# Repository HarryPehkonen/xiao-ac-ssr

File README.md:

# xiao-ac-ssr

One-channel inline AC **solid-state switch** (on/off, no dimming) for a Seeed
Studio XIAO ESP32C3 (or any XIAO on the same 14-pad footprint). Mains cord in
one end, load socket out the other, and a zero-cross opto-triac driving a
snubberless triac switches whatever is plugged in between them. Plug-in
bench/room scale — not house wiring.

Same family as [`xiao-ac-dimmer`](https://github.com/HarryPehkonen/xiao-ac-dimmer):
the whole mains front end, the XIAO sockets, the generator/router pipeline and
the gates are copied; the switching element and everything that existed only to
support *dimming* are replaced.

**Status: schematic and board complete and machine-checked. The board is
150 × 45 mm (67.5 cm²), 11/11 nets routed, DRC clean — 0 errors, 0 warnings.
Gerbers exported but not yet eyeballed in a gerber viewer and not yet checked by
a fab's DFM rules.**

## Why an SSR and not a relay

Mechanical relay contact life at rated load is ~10⁵ operations; 100
activations a day reaches that in a few years, and the contacts weld rather
than fail safe-ly. A triac has no moving contacts. (Seeed's own XIAO relay
module quotes 1.5 × 10⁴ operations at 10 A/250 VAC *resistive* — electrical
endurance, not the headline mechanical number.)

The one thing a triac does **worse** than a relay is fail: it fails **short**,
so the load stays on and software cannot turn it off. See *Safety* below.

## No dimming, therefore much less circuit

Relative to the dimmer, this board **deletes** the H11AA1 zero-cross detector,
both 47 k detector legs, the 10 k pull-up, the 100 Ω + 100 nF triac snubber and
the phase-control firmware — six parts and five nets, all of them on the mains
side. What replaces them:

| | dimmer | this board |
| --- | --- | --- |
| opto | MOC3021M, *random phase* | **MOC3063M, *zero cross*** |
| triac | BTA16-600B, I_GT 50 mA | **BTA16-600SW, I_GT 10 mA, snubberless** |
| gate resistor | 1 k | **360 Ω** (onsemi's own figure-10 value) |
| LED resistor | 220 Ω | **150 Ω** |
| snubber | 100 Ω + 100 nF | none — not needed, see DESIGN.md |
| zero-cross input | H11AA1 on D2 | none; D2 is unused |

The two parts that changed are not cosmetic. A zero-cross opto only conducts
inside a ±12 V (typ) / ±20 V (max) window around the crossing, so the current it
can push into the triac's gate is bounded by that window divided by the gate
resistor. See DESIGN.md for the arithmetic — it is why the *standard* triac
(BTA16-600B, I_GT up to 50 mA) is the wrong part in this position.

## The schematic is generated

`xiao-ac-ssr.kicad_sch` is written by `tools/gen_sch.py`. The circuit lives
there as a table of parts and nets; the generator draws each symbol, a stub wire
per pin and a label naming that pin's net. Open the result in KiCad 9 to review
it like any other schematic.

That indirection is deliberate: a hand-drawn schematic cannot be verified, and
a generated one can (see Gates).

## Gates

```sh
./tools/ci.sh
```

1. **Generator == committed file.** Regenerating leaves `xiao-ac-ssr.kicad_sch`
   and `symbols/xiao-ac.kicad_sym` byte-identical, so neither the committed
   schematic nor the symbol library it draws `J1`/`J2` from is ever stale.
2. **Netlist == intent.** `tools/check_netlist.py` exports a netlist with
   `kicad-cli` and asserts it against the intended netlist: every net present
   with exactly the intended pins, no unintended net at all (that would be a
   short), only the deliberately open pins reported unconnected, and every pin
   of the two XIAO socket rows carrying the *module's* pin name — `D0..D6` on
   `J1`, `VBUS, GND, 3V3_OUT, D10, D9/BOOT, D8, D7` on `J2` — so the schematic
   and its netlist say which pin is which instead of leaving it to a comment.
3. **ERC clean.** `kicad-cli sch erc` reports 0 violations.
4. **Board DRC clean.** `tools/check_board.py` — 0 errors, 0 warnings, including
   the 3 mm mains/logic clearance rule in `xiao-ac-ssr.kicad_dru`.
5. **Board == generator.** `tools/check_regen.py` regenerates the board in a
   throwaway copy of the tools and compares every footprint and every copper
   item against the committed board — 18 footprints (14 parts + 4 mounting
   holes) and 143 tracks+vias today.
   The board file is not *byte*-reproducible (pcbnew stamps fresh UUIDs and
   writes items in its own order), so this compares geometry, which is the part
   a person would have had to edit. `docs/PCB-NOTES.md` has the measurement.
6. **The gates' own tests.** `tools/tests/test_board_gate.py` breaks each
   rule that check 4 enforces — a moved or renamed hole, a track or pad inside
   the keepout, a hole tied to a net, a plated or undersized hole, a footprint
   id with no library nickname, a missing hole — and asserts `check_board.py`
   reports it. `tools/tests/test_pin_names.py` does the same for check 2's pin
   names: a renamed pin, the rows back to `Pin_1..Pin_7`, a renumbered row.
   A rule that has never been seen to fail is not a gate.

Fabrication data:

```sh
./tools/gerbers.sh          # build/gerbers/ + build/xiao-ac-ssr-gerbers.zip
```

## Circuit in one paragraph

Cord hot goes through a 3.15 A fuse, then feeds an MOV, the HLK-PM01's AC input
and the triac's A1; neutral runs straight through to the outlet, unswitched. The
HLK's isolated 5 V reaches the XIAO's VBUS pad through a Schottky diode. GPIO3
(D1) drives the MOC3063M's LED through 150 Ω; the opto's output waits for the
line to cross zero, then pushes current through 360 Ω into the BTA16-600SW's
gate, and the triac conducts the rest of the half-cycle. Part-by-part reasoning,
including the gate-drive arithmetic and what is deliberately *not* proven:
DESIGN.md.

## Bill of materials (all through-hole, 16 parts)

| Ref | Part | Note |
| --- | --- | --- |
| PS1 | HLK-PM01 | isolated 100–240 VAC → 5 V 0.6 A |
| F1 | 5×20 mm fuse clip + 3.15 A slow-blow | hot leg only |
| MOV1 | S14K150 varistor | 150 VAC rating |
| Q1 | BTA16-600SW | TO-220, snubberless logic level, I_GT 10 mA |
| U2 | MOC3063M | *zero-cross* opto-triac, DIP-6 |
| D5 | SS14 | Schottky, VBUS feed |
| R3 | 150 Ω | opto LED from 3.3 V (≈12 mA vs 5 mA I_FT) |
| R4 | 360 Ω | triac gate |
| C1 | 470 µF 16 V | 5 V bulk |
| C2 | 100 nF | XIAO decoupling |
| J1, J2 | 2 × 1×07 2.54 mm socket | XIAO: J1 = D0..D6, J2 = 5V..D7 |
| J3, J4 | 2-pole 5.08 mm screw terminal | cord in / load out |

Where to buy each one, and why: BOM.md.

## Safety — read before powering anything up

- The hot is switched and fused; the neutral is never broken and never fused
  on its own. Mains and logic copper are separated by a 3 mm rule *and* a routed
  isolation slot; nothing on the logic side is ever referenced to mains.
- **A triac fails short.** If Q1 or U2 dies, the load stays energised and no
  software can turn it off. Put a mechanical switch (or a switched cord) between
  the wall and this box, or accept that the only off switch is the breaker.
  A relay fails open instead; this is the price of a moving-contact-free switch.
- **Never work on it live. First power-up on a GFCI/RCD outlet. Never flash
  firmware with mains connected.** Insulation test (500 V) before first
  power-up if a megger is available.
- 3.15 A suits a ~60 W lamp; the ceiling is ~378 W at 120 V because that is what
  1.5 mm mains copper carries at a 10 °C rise (IPC-2221). Larger loads need the
  fuse, the copper *and* the triac's heatsinking rechecked — and the copper is
  currently the binding limit (see DESIGN.md, "the current ceiling").
- Size for **inrush**, not steady wattage: LED drivers and motors pull 10–20×.
  The triac is a 16 A part and will take it; the fuse is slow-blow for the same
  reason.
- Nothing here is a safety certification. The insulation barrier is the
  HLK-PM01, the opto and the layout, and the enclosure is yours. Plastic
  standoffs and a plastic box, never earthed metal.

## Files

```
xiao-ac-ssr.kicad_sch      generated schematic (the reviewable design)
xiao-ac-ssr.kicad_pcb      generated board -- never hand-edit
xiao-ac-ssr.kicad_dru      the 3 mm mains/logic barrier and the 1.5 mm mains width
xiao-ac-ssr.kicad_pro      project + netclass settings
symbols/xiao-ac.kicad_sym  the socket rows' symbols, pins named D0..D6 / VBUS..D7
sym-lib-table fp-lib-table so the libraries resolve without global config
tools/kicadlib.py          s-expression reader, symbol flattening (extends)
tools/gen_sch.py           the circuit + schematic generator
tools/gen_pcb.py           placement + board generator
tools/route.py             the maze router
tools/check_netlist.py     gate: exported netlist == intended netlist (and pin names)
tools/check_board.py       gate: kicad-cli pcb drc, exit 0 = no violations
tools/check_regen.py       gate: committed board == generated board (geometry)
tools/ci.sh                the gates
tools/gerbers.sh           fab output (gerbers, drill, zip)
tools/preview.sh           schematic svg/pdf + board svg, for human eyes
tools/zipdir.py            zip the gerber bundle (zip(1) is not installed here)
docs/PCB-NOTES.md          board status, and what the router needed
docs/ninny-brief.md        the next slice, briefed for a test-first agent
DESIGN.md                  engineering decisions and open items
BOM.md                     sourcing and mechanical notes
```

## Requirements

KiCad 9 (`kicad-cli`) and its Python bindings for the board step; ngspice is not
needed for this board:

```sh
sudo apt-get install kicad kicad-symbols kicad-footprints
```

Regenerate: `python3 tools/gen_sch.py`, then `/usr/bin/python3 tools/gen_pcb.py`
(the `pcbnew` bindings are not in a venv here).

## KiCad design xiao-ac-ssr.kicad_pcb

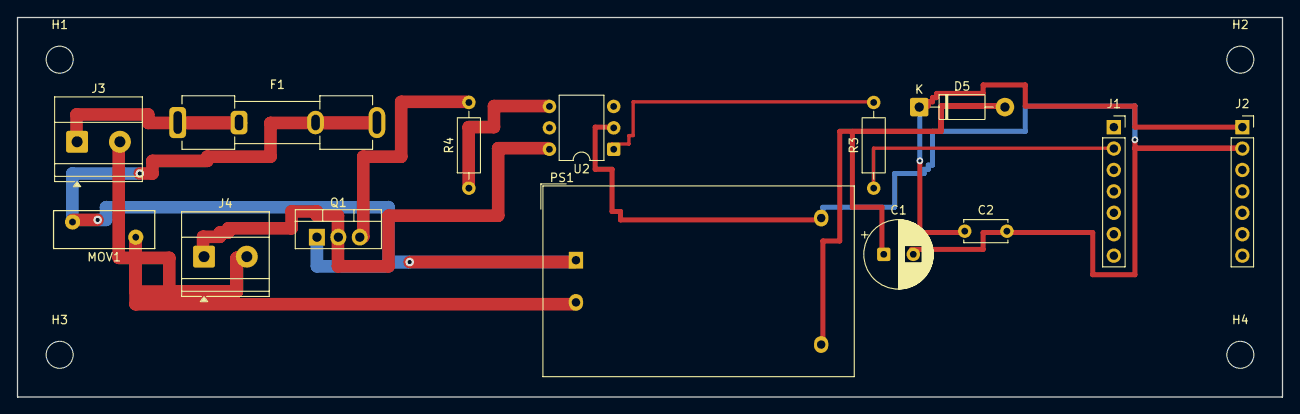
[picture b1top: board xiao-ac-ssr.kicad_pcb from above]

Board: 2 copper layers, 150.0 x 45.0 mm, 18 parts (0 on the bottom side), 11 nets.

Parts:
C1: 470uF 16V; CP_Radial_D8.0mm_P3.50mm
C2: 100nF; C_Disc_D5.0mm_W2.5mm_P5.00mm
D5: SS14; D_DO-41_SOD81_P10.16mm_Horizontal
F1: 3.15A; Fuseholder_Clip-5x20mm_Keystone_3512P_Inline_P23.62x7.27mm_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
H1, H2, H3, H4: MountingHole_3.2mm_M3
J1: XIAO-ESP32C3 left D0..D6; PinSocket_1x07_P2.54mm_Vertical
J2: XIAO-ESP32C3 right 5V..D7; PinSocket_1x07_P2.54mm_Vertical
J3: AC IN (cord); TerminalBlock_Phoenix_MKDS-1,5-2-5.08_1x02_P5.08mm_Horizont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
J4: AC OUT (load); TerminalBlock_Phoenix_MKDS-1,5-2-5.08_1x02_P5.08mm_Horizont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
MOV1: S14K150; RV_Disc_D12mm_W4.5mm_P7.5mm
PS1: HLK-PM01 5V 0.6A; Converter_ACDC_Hi-Link_HLK-PMxx
Q1: BTA16-600SW; TO-220-3_Vertical
R3: 150; R_Axial_DIN0207_L6.3mm_D2.5mm_P10.16mm_Horizontal
R4: 360; R_Axial_DIN0207_L6.3mm_D2.5mm_P10.16mm_Horizontal
U2: MOC3063M; DIP-6_W7.62mm

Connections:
+5V_PS: C1.1, D5.2, PS1.4
+5V_XIAO: C2.1, D5.1, J2.1
GATE_DRV: J1.2, R3.1
GND: C1.2, C2.2, J2.2, PS1.3, U2.2
LOAD_L: J4.1, Q1.2, U2.6
L_FUSED: F1.2, MOV1.1, PS1.1, Q1.1
L_IN: F1.1, J3.1
MOC_A: R3.2, U2.1
MOC_MT2: R4.1, U2.4
N_AC: J3.2, J4.2, MOV1.2, PS1.2
TRIAC_G: Q1.3, R4.2

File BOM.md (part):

# BOM — one board

Generated from the schematic, not typed from memory:

```bash
kicad-cli sch export bom --fields "Reference,Value,Footprint" \
  -o bom.csv xiao-ac-ssr.kicad_sch
```

16 parts. `bom.csv` is the source of truth for values and footprints; this file
adds the part of the BOM a generator cannot know: **where to buy it, and what it
costs to get it here.**

## The sourcing rule

> **Consolidate to the fewest orders first. Origin is a tiebreaker on price, not
> an absolute.** A US-origin part that saves a shipment wins; a $6 saving that
> creates a second shipment loses.

Two constraints in tension, both Harri's:

1. **Non-US origin preferred** — US-origin parts carry tariff and political
   cost. DigiKey's Canadian presence is welcome as a *channel* (one shipment,
   CAD pricing, traceability), not as a statement about origin.
2. **Shipping is per-supplier and it is not small.** DigiKey CA: **free delivery
   at $100 CAD or more; about $15 CAD below that** (their delivery page states
   the $100 threshold; the sub-$100 charge has been reported rising to $15).

So a BOM can carry more shipping than parts. Two ways out: **pad the order over
$100** (spares of the passives are nearly free, and more boards are coming), or
**accept the charge once** rather than paying it several times.

## Where each part comes from

| Source | Parts |
| --- | --- |
| **DigiKey CA** (one order) | `C1` 470 µF 16 V · `C2` 100 nF · `D5` SS14 · `F1` 5×20 mm fuseholder clip + 3.15 A slow-blow · `MOV1` S14K150 · `Q1` BTA16-600SW · `U2` MOC3063M · `R3` 150 Ω · `R4` 360 Ω · `J1`,`J2` 1×07 pin sockets · `J3`,`J4` 5.08 mm 2-pin terminal blocks |
| **AliExpress** | `PS1` HLK-PM01 5 V 3 W (about $1.79 CAD) |
| **Check the drawer first** | `U2` (a MOC3021M is *not* a substitute — see below) · all resistors · 100 nF / 470 µF caps · sockets |

**Check the drawer first, seriously** — but note that this board's two switching
parts are *not* interchangeable with the dimmer's. If you already have a
MOC3021M or a BTA16-600B in the drawer, neither goes on this board:

| part you might have | why it does not go here |
| --- | --- |
| MOC3021M (random phase) | it never waits for the zero crossing — it would switch at whatever phase the firmware happens to drive it, and there is no zero-cross detector on this board to time it with |
| BTA16-600B (standard gate) | I_GT up to 50 mA, and the zero-cross window cannot push that through a sensible gate resistor — see DESIGN.md, "Gate drive" |
| BTA16-600CW / BW (snubberless, 35 / 50 mA) | electrically fine if you accept R4 = 220 Ω (the window bound forces it), and *better* for inductive loads; the 10 mA `SW` is what this board is designed around |

## The two parts that changed, and what to order

| ref | order | note |
| --- | --- | --- |
| `U2` | **Lite-On MOC3063M** (DigiKey 4307927) | zero-cross, 600 V, **5 mA I_FT** grade, DIP-6 — Taiwanese origin *and* the cheapest of the three |
| `Q1` | **ST BTA16-600SW** — order code `BTA16-600SWRG`, DigiKey part number **497-3389-5-ND** (page 669146) | TO-220, 16 A, insulated tab, **I_GT 10 mA**, snubberless logic level |

Checked on DigiKey at the time of writing (single-unit list, USD — **verify at
order; the manufacturer order codes above are the durable part of this table**):

| part | brand | origin | unit | 50-off |
| --- | --- | --- | --- | --- |
| MOC3063M | **Lite-On** | TW | **$0.92** | — |
| MOC3063M | onsemi | US brand, Malaysian assembly | marketplace listing only (Rochester stock; 303,933 available) | — |
| VO3063 | Vishay | US-listed / European opto division | $1.33 | — |
| BTA16-600SWRG | **ST** | CH/IT/FR | **$2.14** | $1.03 |

So the pair is about **$3.06 USD**, and the origin-preferred opto is also the
cheap one — no tension to resolve. `EL3063` (Everlight, TW) is the third
same-spec option if Lite-On is out of stock; it is the same 5 mA I_FT zero-cross
DIP-6 pinout and the same footprint.

**The triac has no origin problem:** ST is Swiss-Italian-French and
`BTA16-600SWRG` is the part the datasheet's Table 4 is written around. There is
a `BTB16-600SW` (non-insulated tab) which is cheaper but needs an insulating pad
under any heatsink — take the `BTA`.

### Why not the DigiKey alternative for PS1

Mean Well IRM-03-5 (`1866-3020-ND`) is the electrical equivalent (5 V 3 W 0.6 A,
85–305 VAC in) and DigiKey stocks it, but: it is a US-brand part at about $8.17
CAD after tariff against $1.79; the swap costs **footprint change plus rerouting
PS1's pads and a re-check of the 3 mm barrier**; and the HLK-PM01's footprint is
already in the design. DigiKey publishes no Hi-Link parts at all. **HLK-PM01
input range: 100–240 VAC, universal** — listings titled "220V to 5V" are using
the Chinese-market convention; it works on North American 120 V mains. Max input
current <0.2 A.

## Mechanical — mounting

Four M3 clearance holes are on the board: one per corner, **5 mm inset** from the
board edge, `MountingHole:MountingHole_3.2mm_M3` — a **non-plated 3.2 mm** hole
with no pad, so nothing is bonded and nothing sits under the screw head. Each
owns a **6 mm copper keepout** (no track, via or pad edge within 3 mm of the hole
centre) and the router blocks that disc, not just the hole.

This is the dimmer's `a32a414` pass applied to this board, which was generated
from the dimmer's tools before it and so had no holes at all:

- The mounting pads stay **isolated** — connected to no net, no copper ring
  under the screw head.
- **Nylon standoffs, not metal.** This is a two-wire appliance with no earth
  conductor, so there is nothing for a metal standoff or a metal enclosure to be
  safely bonded to. Plastic standoffs and a plastic box avoid the question
  entirely.
- Both the holes and the keepout are gated: `tools/check_board.py` checks the
  position, the 3.2 mm non-plated drill, the net and the copper clearance on the
  saved board, and `tools/tests/test_board_gate.py` breaks each of those rules
  one at a time to prove the check has teeth.
- The corner courtyards pushed the packing down 3 mm, and nothing else changed:
  the routing is the pre-hole routing translated 3 mm, item for item. The board
  did **not** grow — see `docs/PCB-NOTES.md`.

## Mechanical — board outline

**150 × 45mm (67.5cm²)**, down from 150 × 95mm (142.5cm²). The 14 parts span
33.8mm top to bottom (y 9 → 42.8mm; y 6 → 39.8mm before the mounting holes
pushed the packing down), so the old 95mm left a **55mm dead band along the
bottom edge** — more than half the board. The outline was inherited
from the dimmer, which had raised its own height to 95mm while the router was
failing; this board was generated from that state, so it inherited the dead band
without ever having had the failure. See `BOARD_H` in `tools/gen_pcb.py`, and
`docs/PCB-NOTES.md` for the measured floor.

## Mechanical — thermal

`Q1` (BTA16-600SW) is the only real heat source. Its dissipation is the on-state
drop times load current, roughly 1.0–1.2 V at 1 A:

| Load | Dissipation | Verdict |
| --- | --- | --- |
| 60 W lamp (~0.5 A) | ~0.6 W | No heatsink. ~35 °C rise on a TO-220 in free air |
| 100 W lamp (~0.85 A) | ~1.0 W | Borderline. ~60 °C rise; a small clip-on heatsink is cheap insurance |
| Board ceiling, 3.15 A | ~3.5–4 W | **Real heatsink required.** ~5 °C/W, tab-mounted |

- **BTA (isolated tab), not BTB.** The `A` part's tab is electrically isolated,
  so a heatsink needs no insulating pad. Keep it heatsink **floating** —
  connected to no net.
- In an **enclosed box** the ambient is 40–50 °C, not 25 °C. Derate accordingly;
  the numbers above assume free air.
- `PS1`, `MOV1` and the fuse are thermally irrelevant at this power level.
- Ventilation in the box is worth more than a bigger heatsink.

## Ordering note — the current ceiling

`F1` stays at 3.15 A, which is what 1.5 mm/1 oz copper carries at a 10 °C rise
(IPC-2221). Do **not** simply fit a bigger fuse to drive a bigger load: the fuse
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
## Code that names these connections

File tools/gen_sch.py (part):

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PARTS = [
    # mains inlet, protection, isolated supply
    {"ref": "J3", "lib": "Connector:Screw_Terminal_01x02", "val": "AC IN (cord)",
     "fp": TERM, "at": (40, 60, 0), "pins": {"1": "L_IN", "2": "N_AC"}},
    {"ref": "F1", "lib": "Device:Fuse", "val": "3.15A", "fp": FUSEHLD,
     "at": (70, 55, 90), "pins": {"1": "L_IN", "2": "L_FUSED"}},
    {"ref": "MOV1", "lib": "Device:Varistor", "val": "S14K150",
     "fp": "Varistor:RV_Disc_D12mm_W4.5mm_P7.5mm", "at": (100, 75, 0),
     "pins": {"1": "L_FUSED", "2": "N_AC"}},
    {"ref": "PS1", "lib": "Converter_ACDC:HLK-PM01", "val": "HLK-PM01 5V 0.6A",
     "fp": "Converter_ACDC:Converter_ACDC_Hi-Link_HLK-PMxx", "at": (60, 120, 0),
     "pins": {"1": "L_FUSED", "2": "N_AC", "3": "GND", "4": "+5V_PS"}},
    # Schottky: Seeed require a diode between an external 5V source and VBUS
    {"ref": "D5", "lib": "Device:D_Schottky", "val": "SS14",
     "fp": "Diode_THT:D_DO-41_SOD81_P10.16mm_Horizontal", "at": (95, 125, 90),
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    # and is unused here, as is the 3V3 pin: this board has no mains-referenced
    # logic side.
    {"ref": "J1", "lib": SYMLIB + ":XIAO_ESP32C3_Left", "val": XIAO_ROWS[0]["value"],
     "fp": SOCK7, "at": (220, 100, 0), "pins": {"2": "GATE_DRV"},
     "nc": ["1", "3", "4", "5", "6", "7"], "ref_dy": -12.7, "val_dy": 12.7},
    {"ref": "J2", "lib": SYMLIB + ":XIAO_ESP32C3_Right", "val": XIAO_ROWS[1]["value"],
     "fp": SOCK7, "at": (255, 100, 0), "pins": {"1": "+5V_XIAO", "2": "GND"},
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    # LED against the part's 5 mA max I_FT (7.5 mA at -40 C), so it triggers
    # cold and triggers on a sagging 3V3 rail.
    {"ref": "R3", "lib": "Device:R", "val": "150", "fp": R_AX,
     "at": (220, 190, 0), "pins": {"1": "GATE_DRV", "2": "MOC_A"}},
    # U2: zero-cross opto-triac.  Its output conducts only inside the zero
    # crossing window (|MT1-MT2| <= V_INH, 12 V typ / 20 V max), so the gate
    # current it can deliver is whatever that window pushes through R4.
    {"ref": "U2", "lib": "Relay_SolidState:MOC3063M", "val": "MOC3063M", "fp": DIP6,
     "at": (245, 190, 0),
     "pins": {"1": "MOC_A", "2": "GND", "4": "MOC_MT2", "6": "LOAD_L"}},
    # 360R is onsemi's own figure-10 value, and it satisfies both bounds: small
    # enough that I_GT is reached inside the inhibit window, large enough that
    # the worst-case surge (peak line / 360) stays under the opto's 1 A I_TSM.
    {"ref": "R4", "lib": "Device:R", "val": "360", "fp": R_AX,
     "at": (275, 200, 0), "pins": {"1": "MOC_MT2", "2": "TRIAC_G"}},
    # snubberless logic-level triac: I_GT 10 mA, so it latches about 4 V into
    # R4 -- comfortably inside the zero-cross window, which is the whole point.
    {"ref": "Q1", "lib": "Triac_Thyristor:BTA16-600SW", "val": "BTA16-600SW",
     "fp": "Package_TO_SOT_THT:TO-220-3_Vertical", "at": (300, 225, 0),
     "pins": {"1": "L_FUSED", "2": "LOAD_L", "3": "TRIAC_G"}},
    # mains outlet (load), neutral unswitched
    {"ref": "J4", "lib": "Connector:Screw_Terminal_01x02", "val": "AC OUT (load)",
     "fp": TERM, "at": (350, 60, 0), "pins": {"1": "LOAD_L", "2": "N_AC"}},
    # ERC: L_IN and N_AC are fed by a passive terminal block
    {"ref": "FLG1", "lib": "power:PWR_FLAG", "val": "PWR_FLAG", "fp": "",
     "at": (40, 85, 0), "pins": {"1": "L_FUSED"}},
    {"ref": "FLG2", "lib": "power:PWR_FLAG", "val": "PWR_FLAG", "fp": "",
     "at": (40, 95, 0), "pins": {"1": "N_AC"}},
]


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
